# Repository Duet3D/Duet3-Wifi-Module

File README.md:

# Duet3 Wifi Module
Plugin wifi module for Duet 3 6HC mainboards

Product Page:
[https://www.duet3d.com/duet3_wifi_module](https://www.duet3d.com/duet3_wifi_module)

Documentation is here:

[Duet 3 Wifi Module Documentation](https://docs.duet3d.com/Duet3D_hardware/Duet_3_family/Duet_3_Mainboard_6HC_Hardware_Overview#wifi-v102)

licensed under the "CERN-OHL-S v2" or any later version plus the "Additional Duet3D Licence Terms",
see https://github.com/Duet3D/Duet3-Mainboard-6HC/blob/master/LICENSE

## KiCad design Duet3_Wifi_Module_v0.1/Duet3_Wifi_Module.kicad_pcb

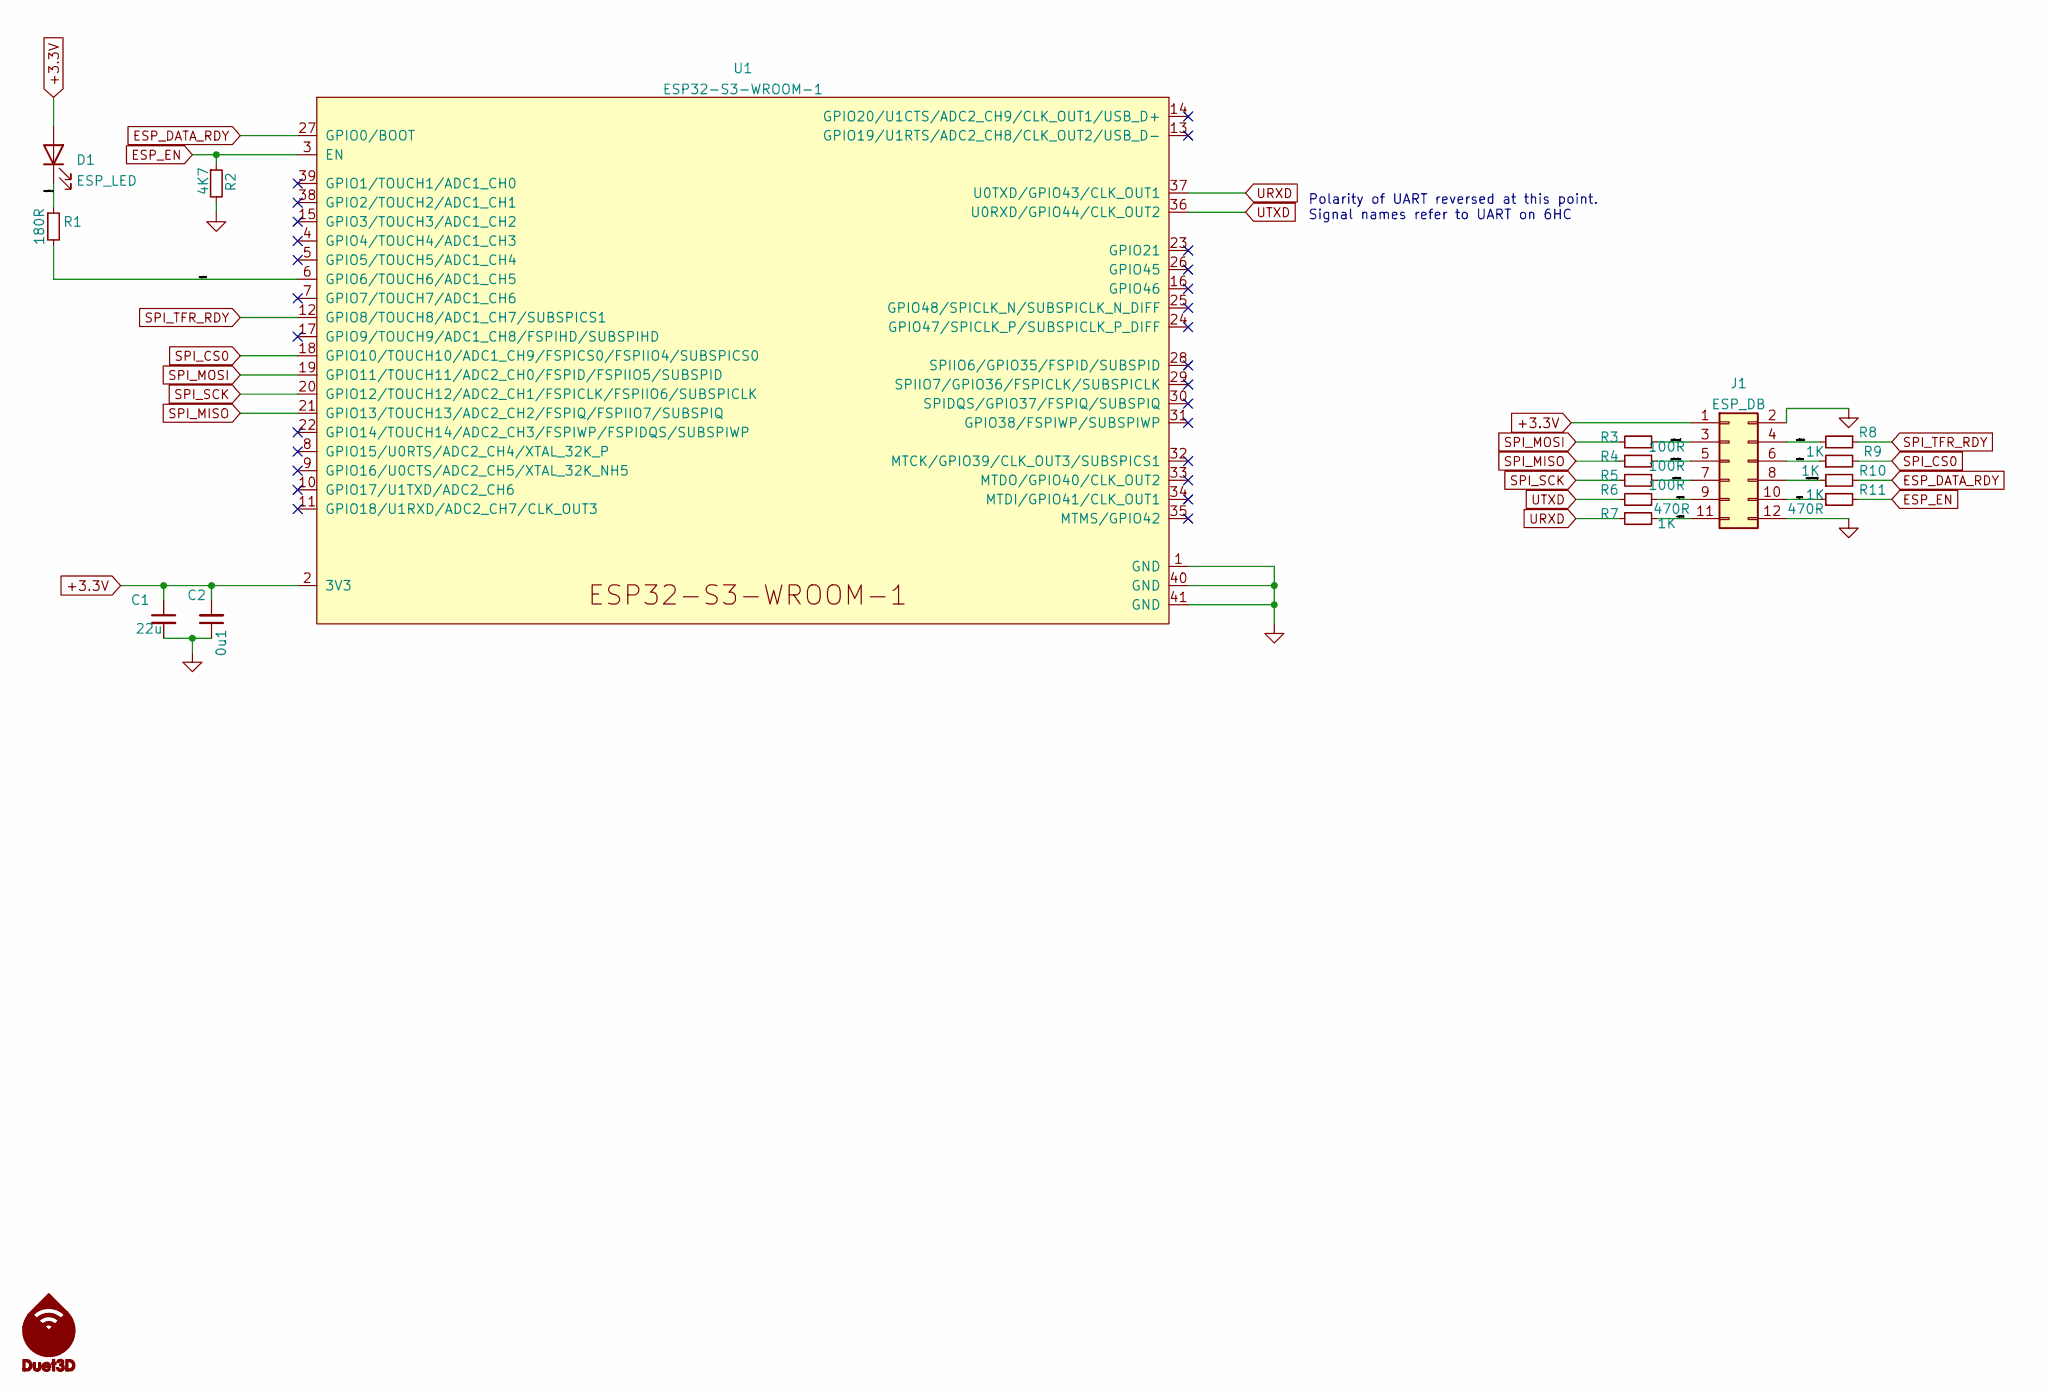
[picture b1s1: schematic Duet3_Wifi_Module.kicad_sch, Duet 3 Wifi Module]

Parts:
C1: 22u; C_0805_2012Metric; Part Number CL21A226MOQNNNE
C2: 0u1; C_0402_1005Metric_Wbry; Part Number CL05A104KP5NNNC
D1: ESP_LED; LED_0603_1608Metric; Part Number 150060VS75000 or equivalent Green
J1: ESP_DB; PinSocket_2x06_P2.54mm_Vertical
M1: Logo_Duet3d_New; LOGO_NEW_Duet3D_vertical_6mm; Part Number Virtual Component DNP
R1: 180R; R_0402_1005Metric_Wbry; Part Number RMCF0402FT180R
R2: 4K7; R_0402_1005Metric_Wbry; Part Number RK73H1ETTP4701F
R3, R4, R5: 100R; R_0402_1005Metric_Wbry; Part Number RK73H1ETTP1000F
R6, R11: 470R; R_0402_1005Metric_Wbry; Part Number RK73H1ETTP4700F
R7, R8, R9, R10: 1K; R_0402_1005Metric_Wbry; Part Number RK73H1ETTP1001F
U1: ESP32-S3-WROOM-1; ESP32-S3-WROOM-1U

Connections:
+3.3V: C1.1, C2.2, D1.2 (A), J1.1, U1.2 (3V3)
/espdatardy: J1.8, R10.1
/espen: J1.10, R11.1
/espled: R1.2, U1.6 (GPIO6/TOUCH6/ADC1_CH5)
/espled_r: D1.1 (K), R1.1
/esprxd: J1.9, R6.1
/esptxd: J1.11, R7.1
/spi1miso: J1.5, R4.1
/spi1mosi: J1.3, R3.1
/spi1sck: J1.7, R5.1
/spi1ss: J1.6, R9.1
/spitfrdy: J1.4, R8.2
ESP_DATA_RDY: R10.2, U1.27 (GPIO0/BOOT)
ESP_EN: R2.1, R11.2, U1.3 (EN)
GND: C1.2, C2.1, J1.2, J1.12, R2.2, U1.1 (GND), U1.40 (GND), U1.41 (GND)
SPI_CS0: R9.2, U1.18 (GPIO10/TOUCH10/ADC1_CH9/FSPICS0/FSPIIO4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)
SPI_MISO: R4.2, U1.21 (GPIO13/TOUCH13/ADC2_CH2/FSPIQ/FSPIIO7/S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)
SPI_MOSI: R3.2, U1.19 (GPIO11/TOUCH11/ADC2_CH0/FSPID/FSPIIO5/S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)
SPI_SCK: R5.2, U1.20 (GPIO12/TOUCH12/ADC2_CH1/FSPICLK/FSPIIO6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)
SPI_TFR_RDY: R8.1, U1.12 (GPIO8/TOUCH8/ADC1_CH7/SUBSPICS1)
URXD: R7.2, U1.37 (U0TXD/GPIO43/CLK_OUT1)
UTXD: R6.2, U1.36 (U0RXD/GPIO44/CLK_OUT2)

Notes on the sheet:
Polarity of UART reversed at this point. Signal names refer to UART on 6HC

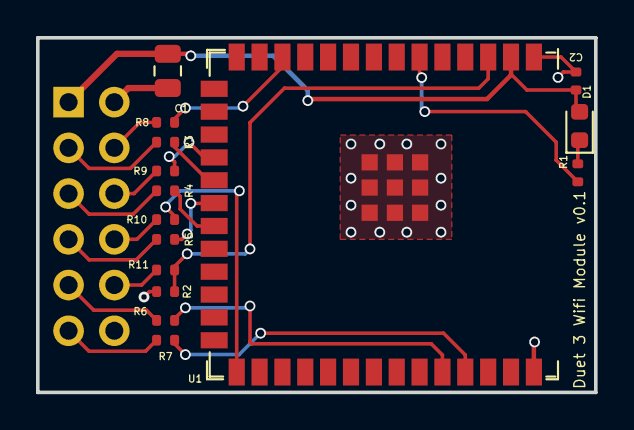
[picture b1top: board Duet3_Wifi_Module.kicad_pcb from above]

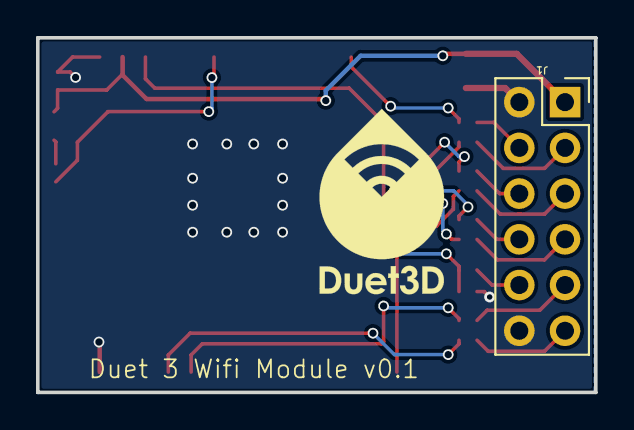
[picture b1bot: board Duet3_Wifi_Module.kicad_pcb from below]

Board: 2 copper layers, 31.0 x 19.7 mm, 17 parts (2 on the bottom side), 22 nets.

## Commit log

2023-07-19 v0.1 source files uploaded
2023-07-19 Added STEP .zip
